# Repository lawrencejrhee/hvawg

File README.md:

# High Voltage Arbitrary Waveform Generator

This is the first draft iteration of a modular arbitrary waveform generator intended to generate possibly tens of separate ±100V 1MHz signals for small capacitive loads, e.g., electrostatic actuators or ion traps.

WARNING: THIS BOARD IS DANGEROUS. IT USES SOMEWHAT HIGH VOLTAGES AT SOMEWHAT HIGH POWER. DO NOT BUILD, TEST, OR USE WITHOUT BOTH CAUTION AND KNOWING WHAT YOU ARE DOING. No guarantees or warranty or support is provided, etc.

Specifications:
- serial data input at 3.3V or 5V up to maybe 100MHz, intended to be driven by FPGA
- 8-bit onboard DAC (with +/-1V output) (ENOB not measured but probably closer to 6 bits)
- amplifier with 100x gain gives outputs ±150V
- maximum output frequency is in the 100kHz range varying with load and voltage
- maximum designed load is tens of picofarads and megaohms of resistance
- up to four boards can be daisy-chained
- quiescent power consumption around 5 to 10W (b/c inefficient class A output stage)
- efficiency ≈1% (b/c inefficient class A output stage in open loop control)
- boards cost about $20 each and use only standard off-the-shelf parts

Measured frequency response:

(generated by feeding external signal into on-board amplifier bypassing DAC)

## Circuit Design

This circuit was made with the following constraints in mind:
- This is primarily intended to drive small capacitive loads, on the order of tens of picofarads with maybe megaohms of resistance. Note that oscilloscope input impedances are also about this much.
- Arbitrary waveform outputs between -100V and +100V and up to 1MHz. Either of those constraints is easy; together they are nontrivial. The ADHV4702 opamp can reach those voltages but only up to about 20kHz, for example.
- In order to have multiple outputs, multiple boards should be able to be daisy chained together. The final design allows up to four boards to be daisy chained and driven off a single 4-wire serial connection (three signals plus GND), for an average of 0.75 input signals per board, to drive as many boards as possible off of a single FPGA or other controller.
- Low cost. If tens of these boards are required for an application, each one should individually be cheap. This resulted in, e.g., five separate power supply inputs. The final part cost per board is around $20. Note a 2-layer PCB was used to decrease manufacturing time for external reasons; switching a 4-layer PCB or better is probably a good idea to allow better EMI mitigation techniques.
- DAC accuracy was not a priority. The original application needed less than 6 bits of resolution.
- Mass production. The circuit should not rely on manually matched transistors for a carefully-balanced amplifier. Instead, the output uses current mirrors that are cheaply implemented with off-the-shelf silicon power MOSFETs and don't require closed loop control on the output (which is not easily achieved at 1MHz at those voltages due to transistor switching time). (There is still manual tuning of amplifier gain and bias in order to minimize cost and accuracy, but this only has to be done once per board.)
- Robustness. The output can probably survive a short-circuit (untested).

The amplifier looks something like the following:

### Alternatives

Previous but insufficient approaches to similar problems include:
- Using a high-voltage op-amp, e.g., the ADHV4702 <https://www.analog.com/en/products/adhv4702-1.html>. This can achieve the +/-100V range but only up to a bit over 20kHz.
- Resonant circuits. Common in ion traps and particle accelerators, but only generate a single specific frequency.
- Discrete amplifiers of assorted topologies, e.g., <https://doi.org/10.1063/1.1988272> or <https://doi.org/10.1063/1.3622750> or <https://www.radiolocman.com/shem/schematics.html?di=637101>. Note also <https://www.falco-systems.com/High_voltage_amplifier_WMA-300.html>. Commonly used for piezoelectric actuator drives, ultrasound, MEMS, or ion traps. These amplifiers achieve the required voltage and frequency specifications but are expensive and/or complex and rely on obscure components.

### Power input

This board takes five power inputs (in addition to the GND connection, of course):
- +12V (1W)
- -12V (1W)
- +100V (5W)
- -100V (5W)
- 12V above the -100V negative rail (1W)

These should be turned on in the following order:
1. +12V
2. -12V
3. +100V
4. -100V
5. 12V above -100V rail

LEDs indicate when the three 12V power supplies are on.

The power supplies used for testing were Wanptek WPS series supplies (160V 2A and 30V 10A) from eBay.

The +/-100V high voltage supplies are used to drive the output and need to be capable of the full board power draw (potentially 10W each, depending on component selection and voltage output).

The +/-12V supplies are used to drive the DAC and intermediate amplifier opamps. These are not generated from the +/-100V because a linear regulator would be too lossy and a buck regulator would make the board significantly more complex and expensive.
Likewise, the low 12V supply is used to drive the output amplifier opamp, and is not generated from the other supplies for the same efficiency reason.

If more convenience is required, an external board can generate the 12V and 100V supplies however desired.

### DAC

The DAC circuit takes a serial input via the 74HC595 shift register and sends the output to a DAC0909 DAC chip.

The DAC is 8 bits. Four PCBs can be daisy-chained together (requiring 32 bits).

The DAC should theoretically operate up to about 100MHz, allowing four 8-bit daisy-chained boards to be updated at above 1MHz. This upper speed has not been tested yet and may be limited by inferior PCB routing.

The DAC protocol works (via the 74HC595) as follows:
- Input signals at 3.3V or 5V should both work.
- 4 pins are required (GND, store_clock, shift_clock, and serial_in).
- First, data is sent in via serial_in at each rising edge of the shift_clock.
- Next, when store_clock is brought high, the current state of the data is saved and sent to the DAC.

This should work with any 74HC595 code, e.g., many Arduino libraries.

### Level shifter

The level shifter circuit accepts an input +/-1V analog signal, translates this into a current, and sends the result to the negative high voltage rail, where it is converted back into an analog voltage to drive the output opamp.

The level shifter can be disconnected from the DAC via jumper JP3 in order to input an external analog signal (e.g., from a low-voltage waveform generator) for testing purposes.

Potentiometer RV1 controls the gain of the high voltage output and should be adjusted to give a 100x amplification.

NOTE: PCBs FABBED FROM PRE-2026-09-09 DESIGN FILES HAVE AN ERROR (see "Errata" below) where the source and drain of PMOS transistor Q3 are switched. If this is not fixed during assembly, when the high voltage low rail is turned on, significant current will flow through R17, which will burn out due to excessive power draw. The design files were corrected on 2026-09-09 (schematic pin mapping + copper reroute, DRC/ERC/netlist verified); boards fabbed from the corrected files take Q3 with straight legs. The exported gerbers under jlcpcb/ are generated from the V2 design revision, which includes this fix.

### High side monitor circuit

This subcircuit provides compensation such that the final high-voltage output is independent of the high voltage supply level (i.e., high voltage inputs of +50V, +100V, and +150V should not affect a 50Vpp output signal).

Potentiometer RV2 controls the DC bias of the output and should be adjusted to center the output at GND = 0V.

Resistor R12=110kohm dissipating up to 200mW was specifically chosen to minimize power draw while also maximizing the voltage/current at the input to opamp U8A (which has nonzero input offset current).

### Output amplifier

This circuit takes an input voltage signal near the negative rail (from the level shifter) and converts this into a current signal through Q1 and R21, which form a class-A amplifier to generate the final high-voltage output. The output voltage is determined by the voltage drop of R21 with the given current.

R21 and Q1, as a class-A amplifier, form a resistive divider between the high voltage power rails, and dissipate a large (10W) current even in their quiescent state in order to drive loads with reasonable accuracy. This means they generate significant heat.

R21 was chosen at 10k as a reasonable compromise between quiescent power draw and load drive ability. R21 can be replaced with a 5kohm power resistor to draw more current but double the output load capacity.

### Output

The final output from R21 and Q1 can be connected to any one of outputs 1 through 4 via jumpers JP8 through JP11.

Four daisy-chained boards can thus be attached to separate outputs.

## Assembly and Testing

### Part choice notes

- All SMD parts are from JLCPCB and specifically chosen from parts with reliable high stock.

- Hand-soldered components were added manually afterward (not through JLCPCB) to reduce order lead time.

### Manufacturing notes

These boards were designed in KiCad and ordered from JLCPCB with help from the excellent kicad-jlc-pcb tools plugin <https://github.com/bouni/kicad-jlcpcb-tools>.

### Assembly notes

Hand assembly of the through hole components takes about 20 minutes per board.

Boards fabbed from pre-2026-09-09 design files: be sure to bend the legs of the PMOS MOSFET (Q3) to switch its source and drain to fix a board error (see "Errata" section below). Boards fabbed from the corrected design files (2026-09-09 or later) install Q3 normally with straight legs — verify which revision a bare board is before assembly.

Header pins are ordered in lenths of 18 to reduce costs. These should be manually cut to size (or ordered in the right size to begin with).

The power resistor R21 needs spare wires soldered on to fit the PCB footprint. The resistor hangs off the edge of the board so it can be bolted to a heatsink. It's possible these spare wires increase EMI emissions. Future board iterations could switch to a TO-220 package power resistor, matching NMOS transistor Q1, which is also at the edge of the board for easy heatsink mounting.

V2 boards (the current design files) mount R21 on the board instead. It is a TO-220 power resistor (LTO050F10001JTE3) laid flat in a small bolt-on heatsink (Wakefield 272-AB), which is screwed to the board and tied to GND. Q1 still goes on a heatsink bar along the board edge. Its tab is at the output voltage, so it needs an insulating pad (Sil-Pad K-10) and a shoulder washer (Keystone 3049). V2 boards also change the connector pinouts, the trimpots (1kohm, wired as rheostats; RV1 now centers the output and RV2 sets the gain) and the power input (J9, a pluggable 8-pin terminal block). On V2 boards the 5kohm R21 option (see Output amplifier) would double R21's dissipation, beyond what the on-board heatsink is sized for. See BRINGUP-V2.md for assembly and bringup, and V2-SUMMARY.md for the full list of changes.

### Bringup notes

The notes below are for V1 boards. V2 boards use BRINGUP-V2.md.

After the board is assembled, the following bringup/test strategy seems to work well:

- Start with jumpers JP3, JP4, and JP6 disconnected. Connect one of JP8, JP9, JP10, JP11 to choose output.
- Test DAC. Apply +12V then -12V supply (if +12V but not -12V is applied too long, DAC may heat up). Confirm LEDs light up. Add DAC input signal. Use thermal camera to confirm no major hot spots (NE5532 opamps at 35°C, LEDs at 32°C, not much else).
- Confirm DAC output is good (TP2/JP3 via oscilloscope). Full scale output is around 2.8Vpp.
- Test high voltage monitor circuit. Attach +120V supply, confirm high voltage monitor output (TP3 via multimeter) is stable and good and in the 1 to 3V range. R12 should rise in temperature (maybe 36°C) due to its 200mW power dissipation.
- Turn off power supplies and add jumpers JP3, JP6.
- Test level shifter. Apply +12V, -12V, +120V, and -120V. Confirm temperatures good (no significant change from before).
- Confirm DAC and monitor outputs remain good.
- Confirm level shifter output is sine wave (measure JP4 oscilloscope with AC coupling).
- Turn supplies off again, add jumper JP4.
- Test final output stage. Turn supplies on, including +12V on negative rail this time (additional LED should come on).
- Confirm only thermal change is output resistor and MOSFET heating to maybe 60-80°C (if supplies are +/-120V).
- Confirm final board output (measured at TP5, output port, or resistor lead via DC-coupled multimeter) is expected signal. Might be DC shifted and cut off at high/low rail.
- Adjust RV2 to center output wave at 0V.
- Adjust RV1 to set gain to get about +/-100V output. Can set to +/-128V full-scale output so that a 1 bit input change results in 1V output change.

### SMD components (JLCPCB)

| Part no.          | QTY | Cost | JLC type | Note                      | URL                                                                    |
|-------------------|-----|------|----------|---------------------------|------------------------------------------------------------------------|
| 74HC595D,118      |   1 | 0.10 | basic    | shift register            | https://jlcpcb.com/partdetail/Nexperia-74HC595D118/C5947               |
| DAC0808LCMX/NOPB  |   1 | 1.80 | extended | dac                       | https://jlcpcb.com/partdetail/TexasInstruments-DAC0808LCMXNOPB/C132006 |
| NE5532DR          |   2 | 0.15 | basic    | opamp                     | https://jlcpcb.com/partdetail/TexasInstruments-NE5532DR/C7426          |
| LM8261M5X/NOPB    |   2 | 2.12 | extended | opamp                     | https://jlcpcb.com/partdetail/TexasInstruments-LM8261M5XNOPB/C7968     |
| L78M05ABDT-TR     |   1 | 0.13 | basic    | 5V regulator              | https://jlcpcb.com/partdetail/Stmicroelectronics-L78M05ABDTTR/C58069   |
| KT-0603W          |   3 | 0.01 | basic    | white 0603 LED            | https://jlcpcb.com/partdetail/Hubei_KentoElec-KT0603W/C2290            |
| RT0402BRE072K74L  |  12 | 0.02 | extended | 2.74kohm 0402 0.1% 62.5mW | https://jlcpcb.com/partdetail/Yageo-RT0402BRE072K74L/C705647           |
| WR20X750JTL       |   1 | 0.02 | extended | 75ohm 2010 200V           | https://jlcpcb.com/partdetail/Walsin_TechCorp-WR20X750JTL/C172257      |
| 1206W4F1004T5E    |   4 | 0.01 | basic    | 1Mohm 1206 200V 250mW     | https://jlcpcb.com/partdetail/18615-1206W4F1004T5E/C17927              |
| UD2D4R7M0810      |   2 | 0.08 | extended | 4.7uF 200V SMD            | https://jlcpcb.com/partdetail/HonorElec-UD2D4R7M0810/C88701            |
| CC0603KRX7R9BB104 |  12 | 0.01 | basic    | 100nF 0603 50V            | https://jlcpcb.com/partdetail/Yageo-CC0603KRX7R9BB104/C14663           |
| CL31A106KBHNNNE   |  13 | 0.03 | basic    | 10uF 1206 50V             | https://jlcpcb.com/partdetail/14236-CL31A106KBHNNNE/C13585             |
| 2010W2J0114T4S    |   1 | 0.01 | extended | 110kohm 2010 200V 500mW   | https://jlcpcb.com/partdetail/21062-2010W2J0114T4S/C20351              |
| CRGP2512F22K      |   1 | 0.41 | unknown  | 22kohm 2512 500V 2W (V2)  | https://www.lcsc.com/datasheet/C2076055.pdf                            |
| CL31B106KAHNNNE   |   1 | 0.19 | extended | 10uF 1206 25V X7R (V2)    | https://jlcpcb.com/partdetail/C14860                                   |

The last two rows are V2 parts: CRGP2512F22K is R30 and CL31B106KAHNNNE is C24. V2 boards also use D4, D5, R26-R29 and R31 (see the schematic). They take 12 of CL31A106KBHNNNE instead of 13, because C24 sits next to the R21 heatsink and must be the X7R part (rated to 125°C, while CL31A106KBHNNNE is X5R and rated to 85°C).

### Through-hole components (manually added afterward)

| Part no.       | QTY | Cost  | Note                  | URL                                                                                           |
|----------------|-----|-------|-----------------------|-----------------------------------------------------------------------------------------------|
| 3296Y-1-472LF  |   2 | $1.3  | 4.7kohm trimpot       | https://www.digikey.com/en/products/detail/bourns-inc/3296Y-1-472LF/2536016                   |
| IRF9610PBF     |   1 | $1.1  | PMOS power FET        | https://www.digikey.com/en/products/detail/vishay-siliconix/IRF9610PBF/811768                 |
| IRF730PBF      |   1 | $1.1  | NMOS power FET        | https://www.digikey.com/en/products/detail/vishay-siliconix/IRF730PBF/811793                  |
| QPC02SXGN-RC   |   4 | $0.04 | jumper                | https://www.digikey.com/en/products/detail/sullins-connector-solutions/QPC02SXGN-RC/2618262   |
| THS2510KJ      |   1 | $2.5  | 10kohm power resistor | https://www.digikey.com/en/products/detail/te-connectivity-passive-product/THS2510KJ/2366983  |
| PREC018SABN-RC |   3 | $0.25 | 18-pin male header    | https://www.digikey.com/en/products/detail/sullins-connector-solutions/PREC018SABN-RC/2775036 |
| PPPC181LGBN-RC |   3 | $0.82 | 18-pin female header  | https://www.digikey.com/en/products/detail/sullins-connector-solutions/PPPC181LGBN-RC/775951  |
| 3296Y-1-102LF  |   2 | -     | 1kohm trimpot (V2)    | https://www.bourns.com/docs/Product-Datasheets/3296.pdf                                       |
| LTO050F10001JTE3 | 1 | $5.1  | 10kohm TO-220 (V2)    | https://www.vishay.com/docs/50050/lto50.pdf                                                   |
| 272-AB         |   1 | $0.79 | TO-220 heatsink (V2)  | https://www.digikey.com/en/products/detail/wakefield-vette/272-AB/345-1043-ND/340341          |
| 1844278        |   1 | $3.26 | J9 header (V2)        | https://www.phoenixcontact.com/en-us/products/pcb-header-mc-15-8-g-35-1844278                 |
| 1840421        |   1 | $9.32 | J9 plug (V2)          | https://www.phoenixcontact.com/en-us/products/pcb-plug-mc-15-8-st-35-1840421                  |

V2 boards use the 1kohm trimpots and LTO050F10001JTE3 instead of the 4.7kohm trimpots and THS2510KJ. They also need two M3 screws with washers and nuts plus non-silicone thermal compound (e.g., Wakefield 126) to mount R21 and its heatsink, and a Sil-Pad K-10 and Keystone 3049 shoulder washer for Q1 (details in BRINGUP-V2.md).

## Errata and Future Improvements

Board error (FIXED in design files 2026-09-09; still applies to boards fabbed before then):
- The PMOS transistor (Q3) source and drain pins are switched on the PCB. On boards fabbed from pre-fix files, this can be fixed when hand-soldering by bending the MOSFET legs to fit the right holes. Not doing this causes excessive current through R17, burning it out, with possible additional damage to RV1.
- Design-file fix (2026-09-09): the Q_PMOS_GDS symbol pin mapping for Q3 was corrected in hvawg.kicad_sch (S=pin 3 to the RV1/U6 network, D=pin 2 to levelshift_out, matching the physical IRF9610 G-D-S pinout), the corresponding pad nets were swapped and copper rerouted in hvawg.kicad_pcb (net "Net-(Q3-D)" renamed "Net-(Q3-S)", zones refilled). Verified: netlist shows Q3 pin 2 on levelshift_out / pin 3 on Net-(Q3-S); DRC and ERC reports are identical to pre-fix baseline (no new violations, 0 unconnected). Boards fabbed from these files install Q3 with straight legs. The exported gerbers and production zip under jlcpcb/ were regenerated for this fix on 2026-09-09 (drill files verified hole-identical; copper carries the corrected nets), and again from the V2 design revision from 2026-09-23 on (each time checked against the board: DRC clean, every drill-hole change accounted for). Regenerate them after any further board change. The BOM/CPL files have not been updated for the V2 parts; regenerate them with the kicad-jlcpcb-tools plugin.
- A safe first-power check for ANY board of unknown revision: set the negative-HV supply current limit to 2 mA and ramp toward -20 V. Reaching full voltage at under ~1 mA means Q3 is correct; pinning at the 2 mA limit with the rail collapsed means the swap is active (the 2 mA ceiling keeps R17 well within its power rating either way).

EMI issue:
- I suspect this board might sometimes generate nontrivial RF noise. Qualitative tests show unshielded wires on the output (or maybe even the wires connecting the through-hole power resistor) generate an undesired signal. Thus, be very careful with board use. Future board iterations should fix this issue by, e.g., more careful PCB trace design and changing the signal output connector to a shielded RF SMA connector or similar.

Improvements:
- The first iteration used a 25W chassis-mount power resistor, which worked fine without heatsinking but needed manual wiring to the PCB. To avoid the inconvenience of having a component not directly mounted to the PCB, future iterations might consider using a TO-220 package power resistor and heatsinking instead (e.g., AP836 10K J, https://www.digikey.com/en/products/detail/ohmite/AP836-10K-J/5878547 ).
- A 2-layer PCB was used to decrease manufacturing time for external reasons; switching a 4-layer PCB or better is probably a good idea to allow better EMI mitigation techniques.

## Images

### 3D render

### Assembled PCBs

### Thermal testing

Note the hottest parts of the circuit are the power resistor and MOSFET near the output, as expected.

### Frequency response testing

An external function generator was used to generate test waveforms by disconnecting the DAC via jumper JP3.

### Daisychain test

### PCB frame concept

Heatsinks, external wires, and control board not included. Note a large flat heatsink is easy to add along the output power resistors and MOSFETs.

### EMI Issue

Several-foot-long unshielded wires connected to the output and a capacitive load interfere with the signal generator. Note the waveform on the oscilloscope only shows half a sinusoid; the lower half was somehow blocked. The test was immediately stopped.

Using a shielded cable reduced interference, but that's still not a perfect sinusoid on the oscilloscope. Recommendation: improve PCB to minimize external wires and other possible EMI sources and use a proper RF SMA connector for the output.

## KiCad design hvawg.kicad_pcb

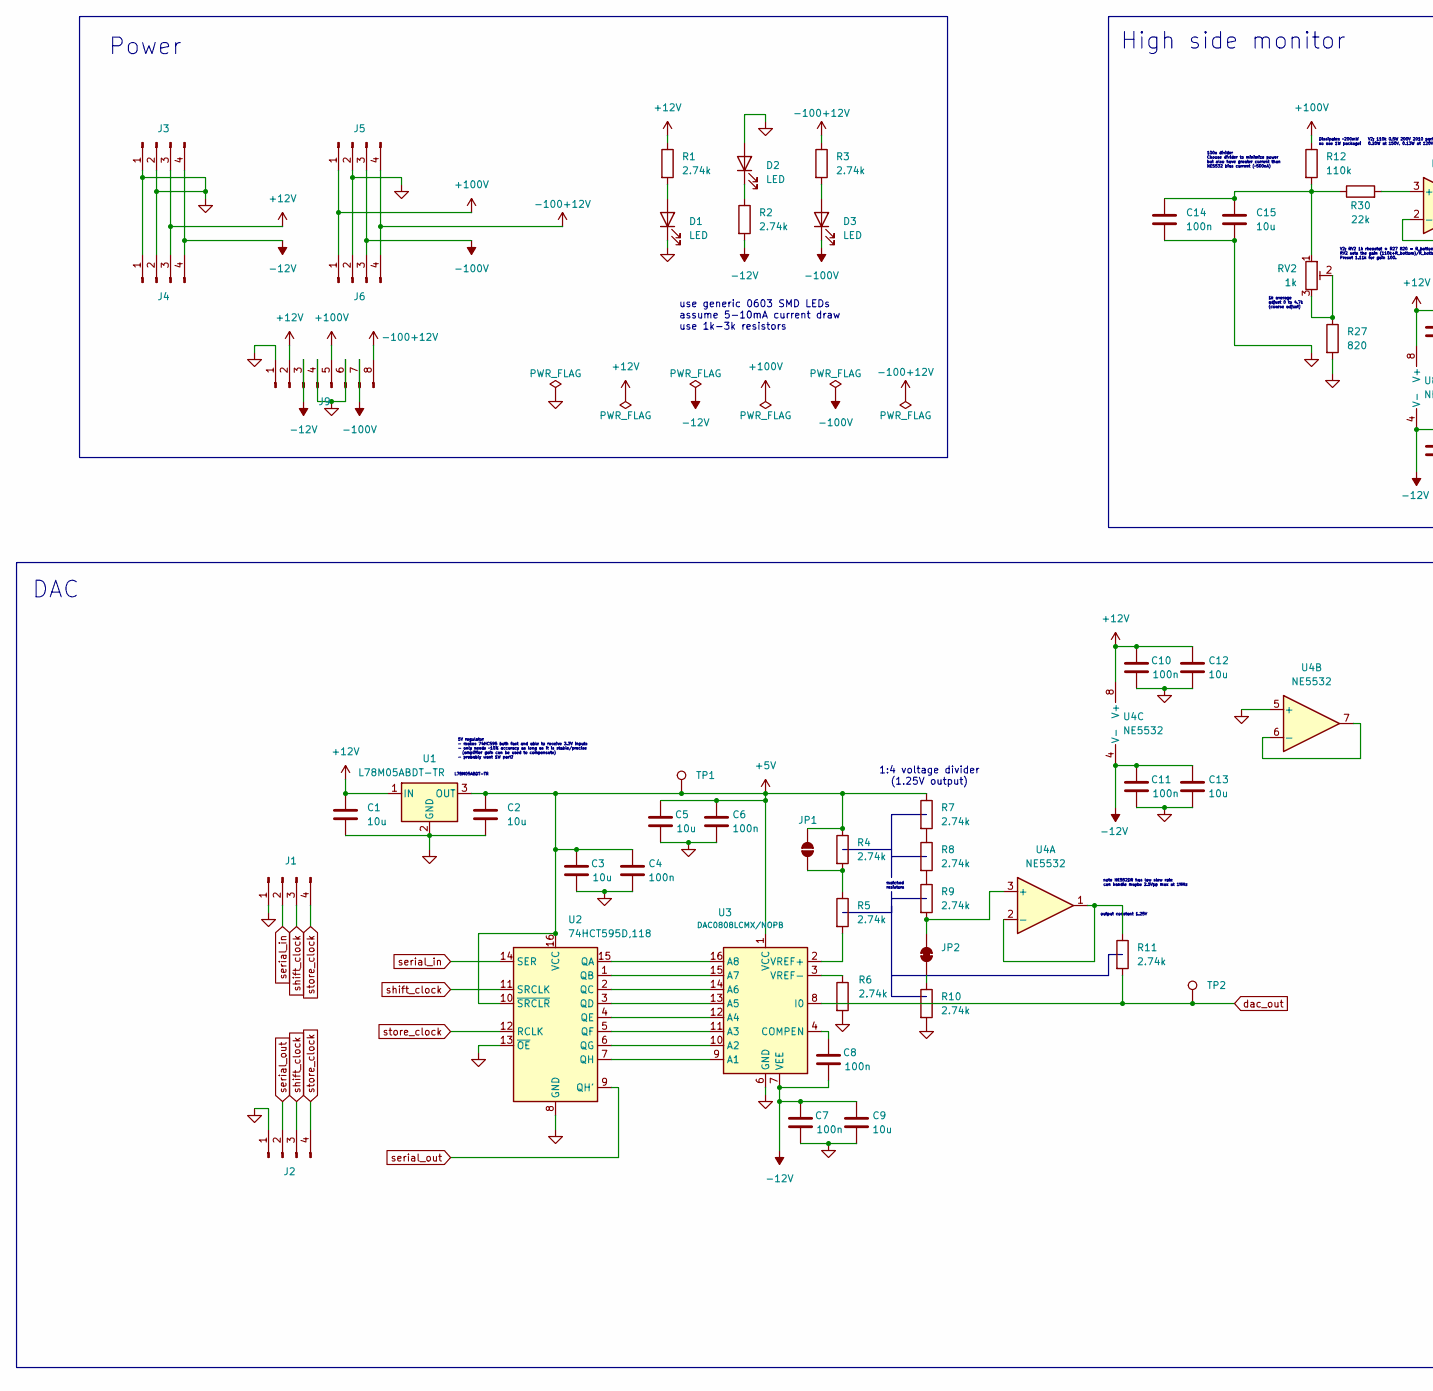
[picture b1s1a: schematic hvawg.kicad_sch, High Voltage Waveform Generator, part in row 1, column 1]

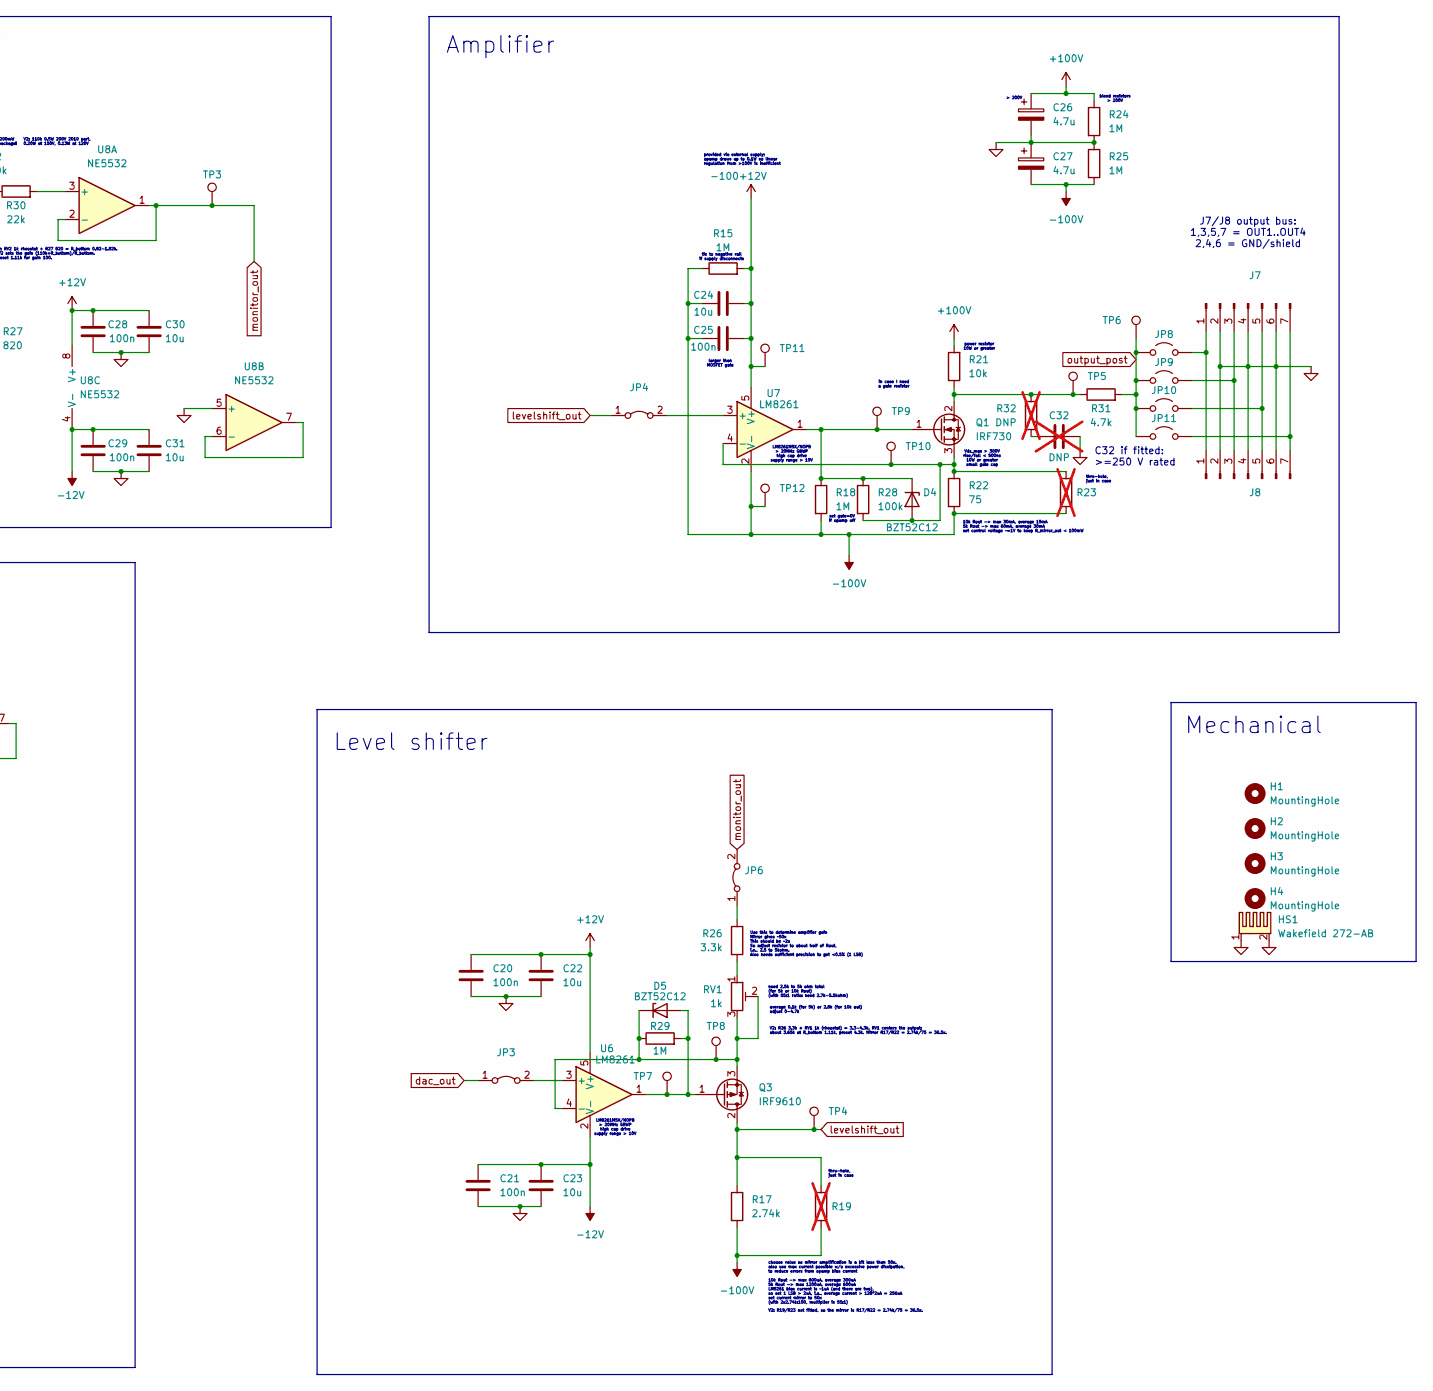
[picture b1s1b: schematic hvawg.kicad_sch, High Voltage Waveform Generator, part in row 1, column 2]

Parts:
C1, C2, C3, C5, C9, C12, C13, C15, C22, C23, C30, C31: 10u; C_1206_3216Metric
C4, C6, C7, C8, C10, C11, C14, C20, C21, C25, C28, C29: 100n; C_0603_1608Metric
C24: 10u; C_1206_3216Metric; MPN CL31B106KAHNNNE
C26, C27: 4.7u; CP_Elec_8x10.5
C32: DNP; C_1206_3216Metric; not fitted
D1, D2, D3: LED; LED_0603_1608Metric
D4, D5: BZT52C12; D_SOD-123; MPN BZT52C12
H1, H2, H3, H4: MountingHole; MountingHole_3.2mm_M3_Pad
HS1: Wakefield 272-AB; Heatsink_Wakefield_272-AB; MPN 272-AB
J1, J3, J5: Conn_01x04_Pin; PinSocket_1x04_P2.54mm_Horizontal_flipped
J2, J4, J6: Conn_01x04_Pin; PinSocket_1x04_P2.54mm_Horizontal
J7: Conn_01x07_Pin; PinSocket_1x07_P2.54mm_Horizontal_flipped
J8: Conn_01x07_Pin; PinSocket_1x07_P2.54mm_Horizontal
J9: Conn_01x08_Pin; PhoenixContact_MC_1,5_8-G-3.5_1x08_P3.50mm_Horizontal_EdgeN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; MPN 1844278
JP1: SolderJumper_2_Open; SolderJumper-2_P1.3mm_Open_RoundedPad1.0x1.5mm
JP2: SolderJumper_2_Bridged; SolderJumper-2_P1.3mm_Bridged_RoundedPad1.0x1.5mm
JP3, JP4, JP6: Jumper_2_Bridged; PinHeader_1x02_P2.54mm_Vertical
JP8, JP9, JP10, JP11: Jumper_2_Open; PinHeader_1x02_P2.54mm_Vertical
Q1: IRF730; TO-220-3_Vertical_HV
Q3: IRF9610; TO-220-3_Vertical_HV
R1, R2, R3, R4, R5, R6, R7, R8, R9, R10, R11, R17: 2.74k; R_0402_1005Metric; MPN RT0402BRE072K74L
R12: 110k; R_2010_5025Metric
R15, R18, R24, R25: 1M; R_1206_3216Metric
R19, R23: 100; R_Axial_DIN0207_L6.3mm_D2.5mm_P2.54mm_Vertical; not fitted
R21: 10k; TO-220-2_Horizontal_LTO50; MPN LTO050F10001JTE3
R22: 75; R_2010_5025Metric
R26: 3.3k; R_0402_1005Metric; MPN 0402WGF3301TCE
R27: 820; R_0402_1005Metric; MPN 0402WGF8200TCE
R28: 100k; R_0402_1005Metric; MPN 0402WGF1003TCE
R29: 1M; R_0402_1005Metric; MPN 0402WGF1004TCE
R30: 22k; R_2512_6332Metric; MPN CRGP2512F22K
R31: 4.7k; R_2512_6332Metric; MPN CRGP2512F4K7
R32: DNP; R_1206_3216Metric; not fitted
RV1, RV2: 1k; Potentiometer_Bourns_3296Y_Vertical
TP1, TP2, TP3, TP4, TP5, TP6, TP7, TP8: TestPoint; TestPoint_Keystone_5005-5009_Compact
TP9, TP10, TP11, TP12: TestPoint; TestPoint_Pad_D1.5mm
U1: L78M05ABDT-TR; TO-252-2; MPN L78M05ABDT-TR
U2: 74HCT595D,118; SOIC-16_3.9x9.9mm_P1.27mm; MPN 74HCT595D,118
U3: DAC0808LCMX/NOPB; SOIC-16_3.9x9.9mm_P1.27mm
U4, U8: NE5532; SOIC-8_3.9x4.9mm_P1.27mm
U6, U7: LM8261; SOT-23-5

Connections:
+5V: C2.1, C3.1, C4.1, C5.1, C6.1, JP1.2 (B), R4.1, R7.1, TP1.1, U1.3 (OUT), U2.10 (~SRCLR), U2.16 (VCC), U3.1 (VCC)
+12V: C1.1, C10.1, C12.1, C20.1, C22.1, C28.1, C30.1, J3.3, J4.3, J9.2, R1.1, U1.1 (IN), U4.8 (V+), U6.5 (V+), U8.8 (V+)
+100V: C26.1, J5.1, J6.1, J9.5, R12.1, R21.2, R24.1
-12V: C7.1, C8.2, C9.1, C11.1, C13.1, C21.1, C23.1, C29.1, C31.1, J3.4, J4.4, J9.3, R2.2, U3.7 (VEE), U4.4 (V-), U6.2 (V-), U8.4 (V-)
-100+12V: C24.2, C25.2, J5.4, J6.4, J9.8, R3.1, R15.2, TP11.1, U7.5 (V+)
-100V: C24.1, C25.1, C27.2, D3.1 (K), J5.3, J6.3, J9.7, R15.1, R17.2, R18.2, R19.2, R22.2, R23.1, R25.2, TP12.1, U7.2 (V-)
GND: C1.2, C2.2, C3.2, C4.2, C5.2, C6.2, C7.2, C9.2, C10.2, C11.2, C12.2, C13.2, C14.2, C15.2, C20.2, C21.2, C22.2, C23.2, C26.2, C27.1, C28.2, C29.2, C30.2, C31.2, C32.2, D1.1 (K), D2.2 (A), HS1.1, HS1.2, J1.1, J2.1, J3.1, J3.2, J4.1, J4.2, J5.2, J6.2, J7.2, J7.4, J7.6, J8.2, J8.4, J8.6, J9.1, J9.4, J9.6, R6.2, R10.2, R24.2, R25.1, R27.2, U1.2 (GND), U2.8 (GND), U2.13 (~OE), U3.6 (GND), U4.5 (+), U8.5 (+)
unnamed: C14.1, C15.1, R12.2, R30.1, RV2.1
unnamed: C32.1, R32.2
unnamed: D1.2 (A), R1.2
unnamed: D2.1 (K), R2.1
unnamed: D3.2 (A), R3.2
unnamed: D4.2 (A), Q1.3 (S), R22.1, R23.2, R28.2, TP10.1, U7.4 (-)
unnamed: D4.1 (K), Q1.1 (G), R18.1, R28.1, TP9.1, U7.1
unnamed: D5.2 (A), Q3.1 (G), R29.2, TP7.1, U6.1
unnamed: D5.1 (K), Q3.3 (S), R29.1, RV1.2, RV1.3, TP8.1, U6.4 (-)
unnamed: J7.1, J8.1, JP8.2 (B)
unnamed: J7.3, J8.3, JP9.2 (B)
unnamed: J7.5, J8.5, JP10.2 (B)
unnamed: J7.7, J8.7, JP11.2 (B)
unnamed: JP1.1 (A), R4.2, R5.1
unnamed: JP2.1 (A), R10.1
unnamed: JP2.2 (B), R9.2, U4.3 (+)
unnamed: JP3.2 (B), U6.3 (+)
unnamed: JP4.2 (B), U7.3 (+)
unnamed: JP6.1 (A), R26.1
unnamed: Q1.2 (D), R21.1, R31.1, R32.1, TP5.1
unnamed: R7.2, R8.1
unnamed: R8.2, R9.1
unnamed: R26.2, RV1.1
unnamed: R27.1, RV2.2, RV2.3
unnamed: U2.15 (QA), U3.16 (A8)
unnamed: U2.1 (QB), U3.15 (A7)
unnamed: U2.2 (QC), U3.14 (A6)
unnamed: U2.3 (QD), U3.13 (A5)
unnamed: U2.4 (QE), U3.12 (A4)
unnamed: U2.5 (QF), U3.11 (A3)
unnamed: U2.6 (QG), U3.10 (A2)
unnamed: U2.7 (QH), U3.9 (A1)
unnamed: C8.1, U3.4 (COMPEN)
unnamed: R5.2, U3.2 (VREF+)
unnamed: R6.1, U3.3 (VREF-)
unnamed: R11.1, U4.1, U4.2 (-)
unnamed: U4.6 (-), U4.7
unnamed: R30.2, U8.3 (+)
unnamed: U8.6 (-), U8.7
dac_out: JP3.1 (A), R11.2, TP2.1, U3.8 (I0)
levelshift_out: JP4.1 (A), Q3.2 (D), R17.1, R19.1, TP4.1
monitor_out: JP6.2 (B), TP3.1, U8.1, U8.2 (-)
output_post: JP8.1 (A), JP9.1 (A), JP10.1 (A), JP11.1 (A), R31.2, TP6.1
serial_in: J1.2, U2.14 (SER)
serial_out: J2.2, U2.9 (QH')
shift_clock: J1.3, J2.3, U2.11 (SRCLK)
store_clock: J1.4, J2.4, U2.12 (RCLK)

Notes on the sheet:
Vds_max > 300V rise/fall < 500ns 10W or greater small gate cap
Level shifter
LM8261M5X/NOPB > 20MHz GBWP high cap drive supply range > 10V
100x divider Choose divider to minimize power but also have greater current than NE5532 bias current (~500nA)
provided via external supply; opamp draws up to 0.1W so linear regulation from >100V is inefficient
average 0.1k (for 5k) or 2.8k (for 10k out) adjust 0-4.7k
1k average adjust 0 to 4.7k (coarse adjust)
use generic 0603 SMD LEDs assume 5-10mA current draw use 1k-3k resistors
L78M05ABDT-TR
Use this to determine amplifier gain Mirror gives ~50x This should be ~2x So adjust resistor to about half of Rout, i.e., 2.5 to 5kohm. Also needs sufficient precision to get <0.5% (1 LSB)
Power
thru-hole, just in case
note NE552DR has low slew rate can handle maybe 2.5Vpp max at 1MHz
in case I need a gate resistor
1:4 voltage divider (1.25V output)
5V regulator - makes 74HC595 both fast and able to receive 3.3V inputs - only needs ~10% accuracy as long as it is stable/precise (amplifier gain can be used to compensate) - probably want 1W part?
> 200V
J7/J8 output bus: 1,3,5,7 = OUT1..OUT4 2,4,6 = GND/shield
larger than MOSFET gate
power resistor 10W or greater
set gate=0V if opamp off
bleed resistors > 200V
DAC
Dissipates ~200mW so use 1W package!
High side monitor
choose value so mirror amplification is a bit less than 50x. also use max current possible w/o excessive power dissipation, to reduce errors from opamp bias current 10k Rout -> max 600uA, average 300uA 5k Rout -> max 1200uA, average 600uA LM8261 bias current is ~1uA (and there are two), so set 1 LS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
output constant 1.25V
Mechanical
matched resistors
10k Rout -> max 30mA, average 15mA 5k Rout -> max 60mA, average 30mA set control voltage ~=1V to keep R_mirror_out < 100mW
tie to negative rail if supply disconnects
Amplifier
need 2.5k to 5k ohm total (for 5k or 10k Rout) (with 55:1 ratio: need 2.7k-5.5kohm)
C32 if fitted: >=250 V rated
V2: R26 3.3k + RV1 1k (rheostat) = 3.3-4.3k. RV1 centers the output: about 3.65k at R_bottom 1.11k, preset 4.3k. Mirror R17/R22 = 2.74k/75 = 36.5x.
V2: R19/R23 not fitted, so the mirror is R17/R22 = 2.74k/75 = 36.5x.
V2: RV2 1k rheostat + R27 820 = R_bottom 0.82-1.82k. RV2 sets the gain (110k+R_bottom)/R_bottom. Preset 1.11k for gain 100.
V2: 110k 0.5W 200V 2010 part, 0.20W at 150V, 0.13W at 120V

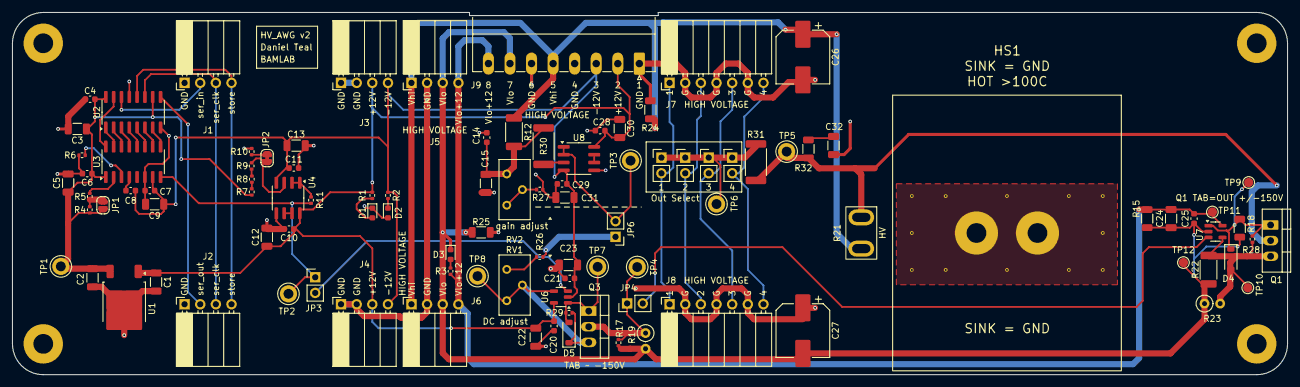
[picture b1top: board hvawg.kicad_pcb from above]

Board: 2 copper layers, 207.0 x 58.8 mm, 107 parts (0 on the bottom side), 54 nets.

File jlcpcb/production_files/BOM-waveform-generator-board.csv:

Comment,Designator,Footprint,LCSC
DAC0808LCMX/NOPB,U3,SOIC-16_3.9x9.9mm_P1.27mm,C132006
10u,"C1,C12,C13,C15,C2,C22,C23,C3,C30,C31,C5,C9",C_1206_3216Metric,C13585
100n,"C10,C11,C14,C20,C21,C25,C28,C29,C4,C6,C7,C8",C_0603_1608Metric,C14663
10u,C24,C_1206_3216Metric,C14860
75,R22,R_2010_5025Metric,C172257
1M,"R15,R18,R24,R25",R_1206_3216Metric,C17927
110k,R12,R_2010_5025Metric,C20351
22k,R30,R_2512_6332Metric,C2076055
LED,"D1,D2,D3",LED_0603_1608Metric,C2290
820,R27,R_0402_1005Metric,C25135
100k,R28,R_0402_1005Metric,C25741
3.3k,R26,R_0402_1005Metric,C25890
1M,R29,R_0402_1005Metric,C26083
"74HCT595D,118",U2,SOIC-16_3.9x9.9mm_P1.27mm,C282339
BZT52C12,"D4,D5",D_SOD-123,C43491
L78M05ABDT-TR,U1,TO-252-2,C58069
2.74k,"R1,R10,R11,R17,R2,R3,R4,R5,R6,R7,R8,R9",R_0402_1005Metric,C705647
NE5532,"U4,U8",SOIC-8_3.9x4.9mm_P1.27mm,C7426
LM8261,"U6,U7",SOT-23-5,C7968
4.7u,"C26,C27",CP_Elec_8x10.5,C88701

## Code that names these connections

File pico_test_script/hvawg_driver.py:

# HVAWG 4-channel driver for Raspberry Pi Pico / Pico 2 (MicroPython)
#
# Drives up to 4 daisy-chained boards (4x 74HC595 -> 4x DAC0808) as one 32-bit
# shift chain, converting a commanded HV OUTPUT VOLTAGE per channel into the
# right 8-bit DAC code using per-board calibration.
#
# Wiring (Pico -> J1 input header of the FIRST / nearest board):
#   GP3 -> J1 pin 2  serial_in    (SPI0 MOSI / TX)
#   GP2 -> J1 pin 3  shift_clock  (SPI0 SCK)
#   GP5 -> J1 pin 4  store_clock  (manual GPIO latch, broadcast to all boards)
#   GND -> J1 pin 1  GND          (mandatory common ground)
# Each board's serial_out (74HC595 QH'/pin 9) -> next board's serial_in.
# shift_clock and store_clock are broadcast to every board.
#
# Logic levels: you have ALREADY confirmed 3.3V drive works on this board
# (the DAC sine appeared at TP2 driven by the Pico). The README also states
# 3.3V/5V inputs both work. (Datasheet VIH at VCC=5V is 3.5V, so it's
# technically marginal -- but it's empirically fine here.)
# Boards built from the V2 rev 2 BOM fit a 74HCT595 instead (VIH 2.0V at 5V),
# so 3.3V drive is in spec on those.

from machine import Pin, SPI
import time

# ---------- PER-CHANNEL CALIBRATION (MEASURE THESE PER BOARD) ----------
# Model is the linear fit of the HV OUTPUT (TP5) vs DAC code, at the ACTUAL
# rails you run (you're at +/-50V):
#         V_out = slope * code + intercept            (code 0..255)
# To command a voltage we invert it:
#         code  = round((V_target - intercept) / slope)
#
# How to get the numbers (see hardware step H2):
#   1. Trim RV2 so code 128 reads ~0V at TP5, RV1 for your full-scale.
#   2. Sweep codes (0,64,128,192,255), read TP5 with a DMM.
#   3. Least-squares fit V_out = slope*code + intercept.
#   The slope is NEGATIVE: the DAC stage inverts, so the output FALLS as the
#   code rises (code 0 -> about +125 V requested, code 128 -> ~0 V,
#   code 255 -> about -124 V). The request is clipped at the actual rails,
#   so at +/-50 V rails only codes ~77..179 are linear.
#   slope     ~= -100 * (DAC V/code) ~= -0.98 V/code (gain ~100, DAC ~2.49 Vpp)
#   intercept ~= volts at code 0 ~= +125 V (extrapolated; beyond the rails)
#   Fit only the codes that are NOT clipped at your rail voltage.
# These are PER BOARD (RV1/RV2 differ) and NOT transferable -- tag to a serial #.
# The values below are PLACEHOLDERS from the design analysis; replace them with
# your board's measured fit before trusting any commanded voltage.
CAL = [
    {"slope": -0.976, "intercept": 125.0},  # ch0 = NEAREST board (last byte shifted)
    {"slope": -0.976, "intercept": 125.0},  # ch1
    {"slope": -0.976, "intercept": 125.0},  # ch2
    {"slope": -0.976, "intercept": 125.0},  # ch3 = FARTHEST board (first byte shifted)
]


class HVAWG:
    NUM_CH     = 4
    V_MAX      = 45.0     # software clamp (V). Keep < rail (~49V) for headroom.
    TIMEOUT_MS = 100      # watchdog: no valid setpoint within this -> failsafe to 0V

    def __init__(self, data_gp=3, clock_gp=2, latch_gp=5, cal=CAL, use_spi=True):
        assert len(cal) == self.NUM_CH, "CAL must have NUM_CH entries"
        self.cal = cal
        self._latch = Pin(latch_gp, Pin.OUT, value=0)
        self._spi = None
        if use_spi:
            # 74HC595 is SPI mode 0 (idle low, sample on rising), MSB-first.
            # GP2 = SPI0 SCK, GP3 = SPI0 TX(MOSI) on RP2040/RP2350 -- required.
            self._spi = SPI(0, baudrate=4_000_000, polarity=0, phase=0,
                            bits=8, firstbit=SPI.MSB,
                            sck=Pin(clock_gp), mosi=Pin(data_gp))
        else:                                    # bit-bang fallback (slower, jittery)
            self._data  = Pin(data_gp,  Pin.OUT, value=0)
            self._clock = Pin(clock_gp, Pin.OUT, value=0)
        self._last_feed = time.ticks_ms()

    # ---- voltage -> code (invert the per-board fit; clamp in VOLTS first) ----
    def volts_to_code(self, ch, v):
        if v >  self.V_MAX: v =  self.V_MAX      # CLAMP before convert (no int wrap!)
        if v < -self.V_MAX: v = -self.V_MAX
        c = self.cal[ch]
        code = int(round((v - c["intercept"]) / c["slope"]))
        if code < 0:   code = 0                   # clip to valid DAC range
        if code > 255: code = 255
        return code

    # ---- low-level: shift all 4 bytes, then ONE atomic latch ----
    def set_codes(self, codes):
        assert len(codes) == self.NUM_CH
        # First byte shifted travels FURTHEST -> lands on the farthest board.
        # So transmit ch3 (farthest) first ... ch0 (nearest) last.
        frame = bytes(codes[i] for i in range(self.NUM_CH - 1, -1, -1))
        self._latch.value(0)                      # outputs hold previous value
        if self._spi:
            self._spi.write(frame)
        else:
            for byte in frame:
                for i in range(7, -1, -1):        # MSB first
                    self._data.value((byte >> i) & 1)
                    self._clock.value(1)          # rising edge shifts the bit
                    self._clock.value(0)
        self._latch.value(1)                      # single rising edge -> all 4 latch
        # leave latch HIGH; next call drives it low before shifting

    # ---- high-level: volts in, HV out ----
    def set_channels(self, volts):
        codes = [self.volts_to_code(ch, volts[ch]) for ch in range(self.NUM_CH)]
        self.set_codes(codes)
        return codes                              # echo applied codes for logging

    def all_zero(self):
        self.set_channels([0.0] * self.NUM_CH)

    # ---- watchdog (feed ONLY on a valid setpoint; never in the failsafe) ----
    def feed(self):
        self._last_feed = time.ticks_ms()

    def expired(self):
        return time.ticks_diff(time.ticks_ms(), self._last_feed) > self.TIMEOUT_MS
